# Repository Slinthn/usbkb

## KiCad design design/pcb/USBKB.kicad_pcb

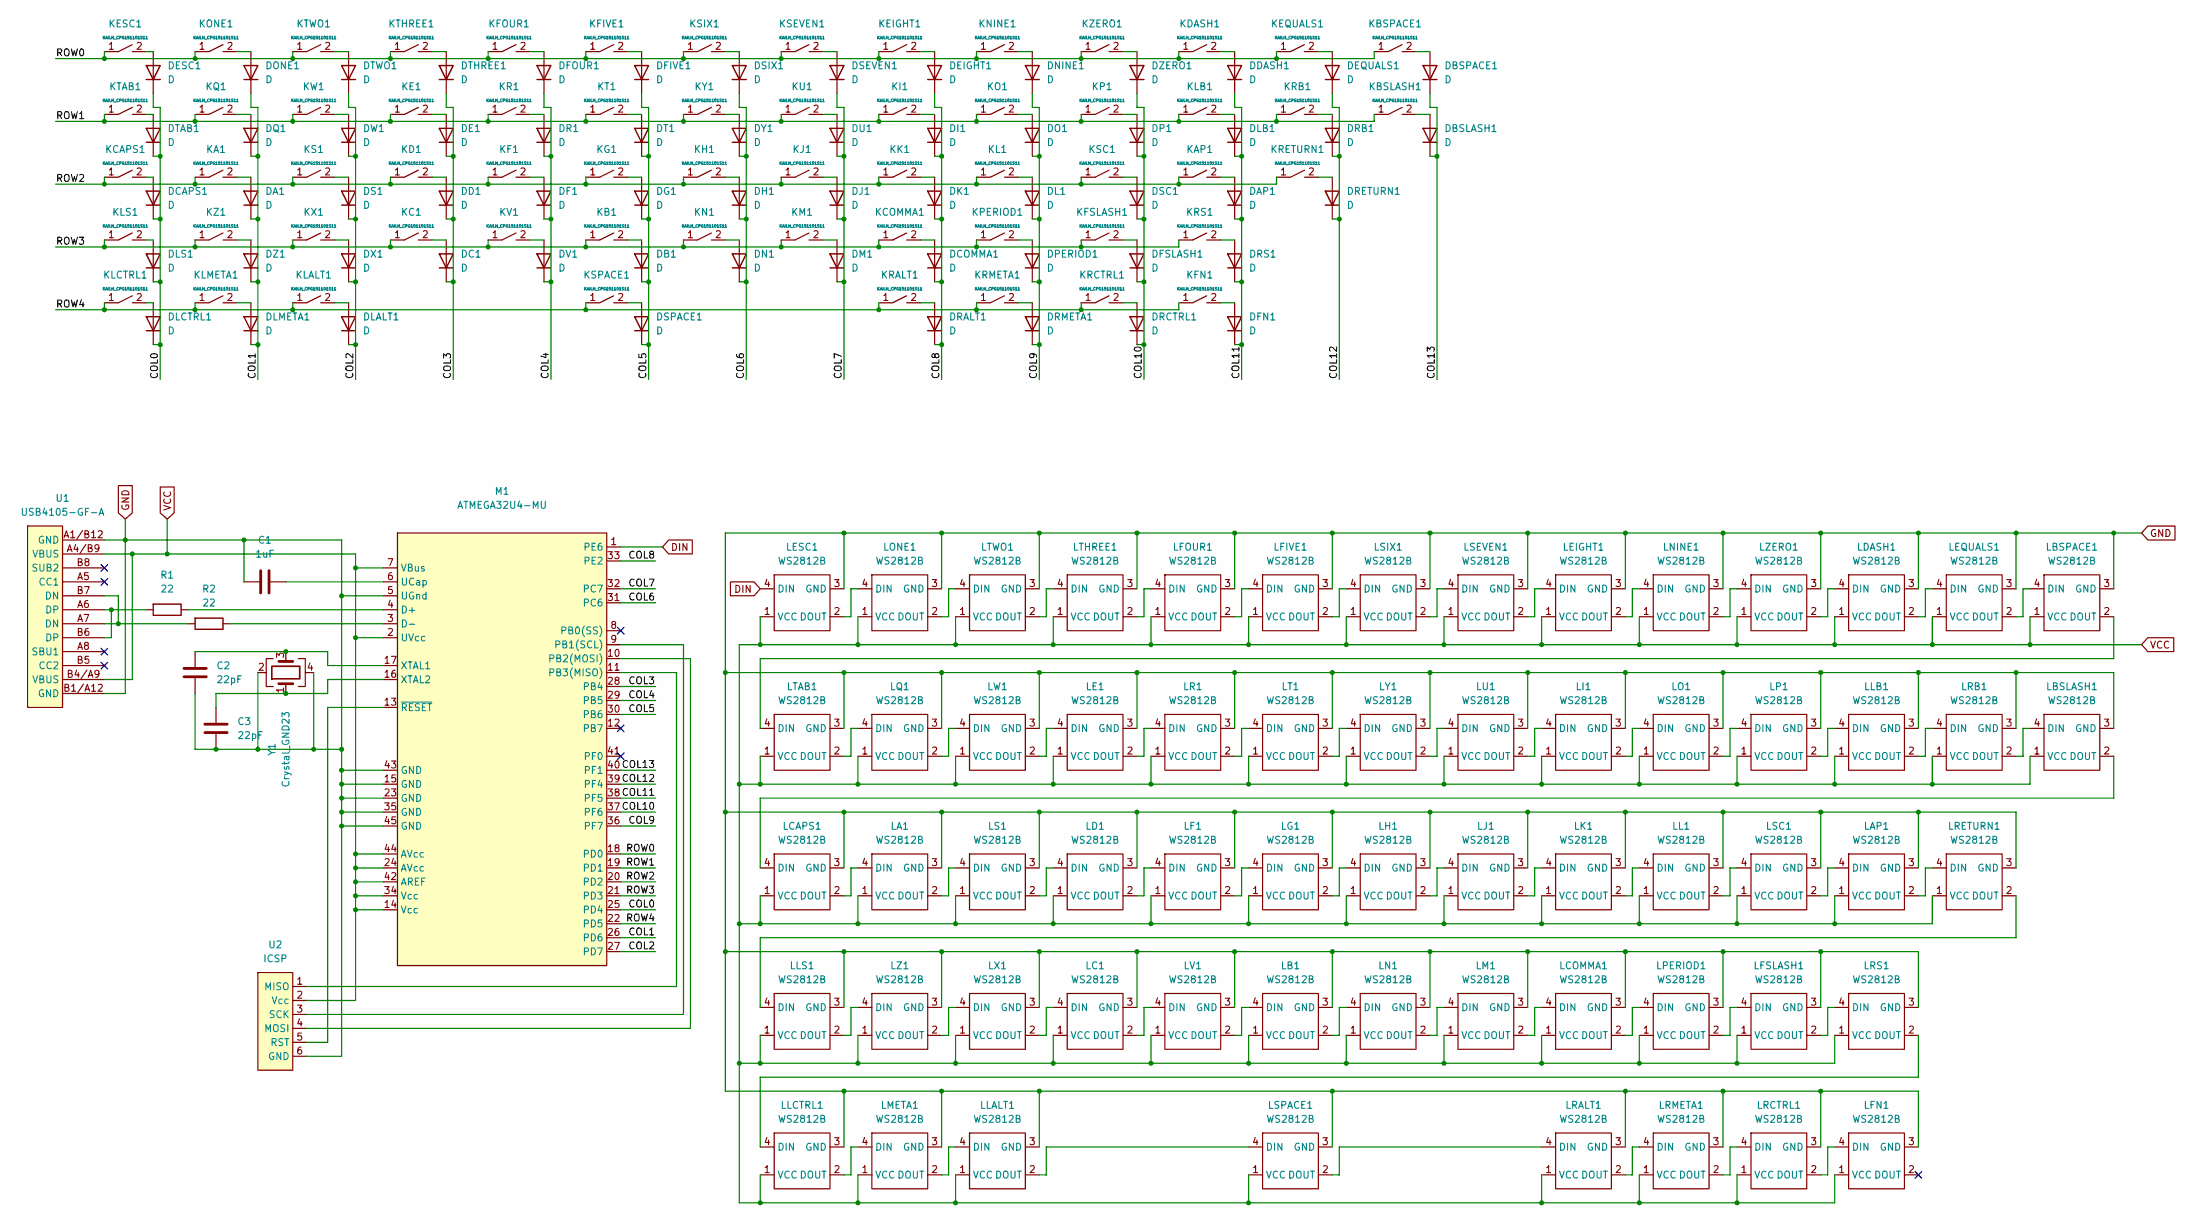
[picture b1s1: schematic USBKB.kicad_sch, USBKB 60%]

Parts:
C1: 1uF; 0805
C2, C3: 22pF; 0805
DA1: D; 1N4148WX
DAP1: D; 1N4148WX
DB1: D; 1N4148WX
DBSLASH1: D; 1N4148WX
DBSPACE1: D; 1N4148WX
DC1: D; 1N4148WX
DCAPS1: D; 1N4148WX
DCOMMA1: D; 1N4148WX
DD1: D; 1N4148WX
DDASH1: D; 1N4148WX
DE1: D; 1N4148WX
DEIGHT1: D; 1N4148WX
DEQUALS1: D; 1N4148WX
DESC1: D; 1N4148WX
DF1: D; 1N4148WX
DFIVE1: D; 1N4148WX
DFN1: D; 1N4148WX
DFOUR1: D; 1N4148WX
DFSLASH1: D; 1N4148WX
DG1: D; 1N4148WX
DH1: D; 1N4148WX
DI1: D; 1N4148WX
DJ1: D; 1N4148WX
DK1: D; 1N4148WX
DL1: D; 1N4148WX
DLALT1: D; 1N4148WX
DLB1: D; 1N4148WX
DLCTRL1: D; 1N4148WX
DLMETA1: D; 1N4148WX
DLS1: D; 1N4148WX
DM1: D; 1N4148WX
DN1: D; 1N4148WX
DNINE1: D; 1N4148WX
DO1: D; 1N4148WX
DONE1: D; 1N4148WX
DP1: D; 1N4148WX
DPERIOD1: D; 1N4148WX
DQ1: D; 1N4148WX
DR1: D; 1N4148WX
DRALT1: D; 1N4148WX
DRB1: D; 1N4148WX
DRCTRL1: D; 1N4148WX
DRETURN1: D; 1N4148WX
DRMETA1: D; 1N4148WX
DRS1: D; 1N4148WX
DS1: D; 1N4148WX
DSC1: D; 1N4148WX
DSEVEN1: D; 1N4148WX
DSIX1: D; 1N4148WX
DSPACE1: D; 1N4148WX
DT1: D; 1N4148WX
DTAB1: D; 1N4148WX
DTHREE1: D; 1N4148WX
DTWO1: D; 1N4148WX
DU1: D; 1N4148WX
DV1: D; 1N4148WX
DW1: D; 1N4148WX
DX1: D; 1N4148WX
DY1: D; 1N4148WX
DZ1: D; 1N4148WX
DZERO1: D; 1N4148WX
KA1: KAILH_CPG151101S11; KAILH-CPG151101S11-1U
KAP1: KAILH_CPG151101S11; KAILH-CPG151101S11-1U
KB1: KAILH_CPG151101S11; KAILH-CPG151101S11-1U
KBSLASH1: KAILH_CPG151101S11; KAILH-CPG151101S11-1.5U
KBSPACE1: KAILH_CPG151101S11; KAILH-CPG151101S11-2U
KC1: KAILH_CPG151101S11; KAILH-CPG151101S11-1U
KCAPS1: KAILH_CPG151101S11; KAILH-CPG151101S11-1.75U
KCOMMA1: KAILH_CPG151101S11; KAILH-CPG151101S11-1U
KD1: KAILH_CPG151101S11; KAILH-CPG151101S11-1U
KDASH1: KAILH_CPG151101S11; KAILH-CPG151101S11-1U
KE1: KAILH_CPG151101S11; KAILH-CPG151101S11-1U
KEIGHT1: KAILH_CPG151101S11; KAILH-CPG151101S11-1U
KEQUALS1: KAILH_CPG151101S11; KAILH-CPG151101S11-1U
KESC1: KAILH_CPG151101S11; KAILH-CPG151101S11-1U
KF1: KAILH_CPG151101S11; KAILH-CPG151101S11-1U
KFIVE1: KAILH_CPG151101S11; KAILH-CPG151101S11-1U
KFN1: KAILH_CPG151101S11; KAILH-CPG151101S11-1.25U
KFOUR1: KAILH_CPG151101S11; KAILH-CPG151101S11-1U
KFSLASH1: KAILH_CPG151101S11; KAILH-CPG151101S11-1U
KG1: KAILH_CPG151101S11; KAILH-CPG151101S11-1U
KH1: KAILH_CPG151101S11; KAILH-CPG151101S11-1U
KI1: KAILH_CPG151101S11; KAILH-CPG151101S11-1U
KJ1: KAILH_CPG151101S11; KAILH-CPG151101S11-1U
KK1: KAILH_CPG151101S11; KAILH-CPG151101S11-1U
KL1: KAILH_CPG151101S11; KAILH-CPG151101S11-1U
KLALT1: KAILH_CPG151101S11; KAILH-CPG151101S11-1.25U
KLB1: KAILH_CPG151101S11; KAILH-CPG151101S11-1U
KLCTRL1: KAILH_CPG151101S11; KAILH-CPG151101S11-1.25U
KLMETA1: KAILH_CPG151101S11; KAILH-CPG151101S11-1.25U
KLS1: KAILH_CPG151101S11; KAILH-CPG151101S11-2.25U
KM1: KAILH_CPG151101S11; KAILH-CPG151101S11-1U
KN1: KAILH_CPG151101S11; KAILH-CPG151101S11-1U
KNINE1: KAILH_CPG151101S11; KAILH-CPG151101S11-1U
KO1: KAILH_CPG151101S11; KAILH-CPG151101S11-1U
KONE1: KAILH_CPG151101S11; KAILH-CPG151101S11-1U
KP1: KAILH_CPG151101S11; KAILH-CPG151101S11-1U
KPERIOD1: KAILH_CPG151101S11; KAILH-CPG151101S11-1U
KQ1: KAILH_CPG151101S11; KAILH-CPG151101S11-1U
KR1: KAILH_CPG151101S11; KAILH-CPG151101S11-1U
KRALT1: KAILH_CPG151101S11; KAILH-CPG151101S11-1.25U
KRB1: KAILH_CPG151101S11; KAILH-CPG151101S11-1U
KRCTRL1: KAILH_CPG151101S11; KAILH-CPG151101S11-1.25U
KRETURN1: KAILH_CPG151101S11; KAILH-CPG151101S11-2.25U
KRMETA1: KAILH_CPG151101S11; KAILH-CPG151101S11-1.25U
KRS1: KAILH_CPG151101S11; KAILH-CPG151101S11-2.75U
KS1: KAILH_CPG151101S11; KAILH-CPG151101S11-1U
KSC1: KAILH_CPG151101S11; KAILH-CPG151101S11-1U
KSEVEN1: KAILH_CPG151101S11; KAILH-CPG151101S11-1U
KSIX1: KAILH_CPG151101S11; KAILH-CPG151101S11-1U
KSPACE1: KAILH_CPG151101S11; KAILH-CPG151101S11-6.25U
KT1: KAILH_CPG151101S11; KAILH-CPG151101S11-1U
KTAB1: KAILH_CPG151101S11; KAILH-CPG151101S11-1.5U
KTHREE1: KAILH_CPG151101S11; KAILH-CPG151101S11-1U
KTWO1: KAILH_CPG151101S11; KAILH-CPG151101S11-1U
KU1: KAILH_CPG151101S11; KAILH-CPG151101S11-1U
KV1: KAILH_CPG151101S11; KAILH-CPG151101S11-1U
KW1: KAILH_CPG151101S11; KAILH-CPG151101S11-1U
KX1: KAILH_CPG151101S11; KAILH-CPG151101S11-1U
KY1: KAILH_CPG151101S11; KAILH-CPG151101S11-1U
KZ1: KAILH_CPG151101S11; KAILH-CPG151101S11-1U
KZERO1: KAILH_CPG151101S11; KAILH-CPG151101S11-1U
LA1: WS2812B; SK6812MINI-E
LAP1: WS2812B; SK6812MINI-E
LB1: WS2812B; SK6812MINI-E
LBSLASH1: WS2812B; SK6812MINI-E
LBSPACE1: WS2812B; SK6812MINI-E
LC1: WS2812B; SK6812MINI-E
LCAPS1: WS2812B; SK6812MINI-E
LCOMMA1: WS2812B; SK6812MINI-E
LD1: WS2812B; SK6812MINI-E
LDASH1: WS2812B; SK6812MINI-E
LE1: WS2812B; SK6812MINI-E
LEIGHT1: WS2812B; SK6812MINI-E
LEQUALS1: WS2812B; SK6812MINI-E
LESC1: WS2812B; SK6812MINI-E
LF1: WS2812B; SK6812MINI-E
LFIVE1: WS2812B; SK6812MINI-E
LFN1: WS2812B; SK6812MINI-E
LFOUR1: WS2812B; SK6812MINI-E
LFSLASH1: WS2812B; SK6812MINI-E
LG1: WS2812B; SK6812MINI-E
LH1: WS2812B; SK6812MINI-E
LI1: WS2812B; SK6812MINI-E
LJ1: WS2812B; SK6812MINI-E
LK1: WS2812B; SK6812MINI-E
LL1: WS2812B; SK6812MINI-E
LLALT1: WS2812B; SK6812MINI-E
LLB1: WS2812B; SK6812MINI-E
LLCTRL1: WS2812B; SK6812MINI-E
LLS1: WS2812B; SK6812MINI-E
LM1: WS2812B; SK6812MINI-E
LMETA1: WS2812B; SK6812MINI-E
LN1: WS2812B; SK6812MINI-E
LNINE1: WS2812B; SK6812MINI-E
LO1: WS2812B; SK6812MINI-E
LONE1: WS2812B; SK6812MINI-E
LP1: WS2812B; SK6812MINI-E
LPERIOD1: WS2812B; SK6812MINI-E
LQ1: WS2812B; SK6812MINI-E
LR1: WS2812B; SK6812MINI-E
LRALT1: WS2812B; SK6812MINI-E
LRB1: WS2812B; SK6812MINI-E
LRCTRL1: WS2812B; SK6812MINI-E
LRETURN1: WS2812B; SK6812MINI-E
LRMETA1: WS2812B; SK6812MINI-E
LRS1: WS2812B; SK6812MINI-E
LS1: WS2812B; SK6812MINI-E
LSC1: WS2812B; SK6812MINI-E
LSEVEN1: WS2812B; SK6812MINI-E
LSIX1: WS2812B; SK6812MINI-E
LSPACE1: WS2812B; SK6812MINI-E
LT1: WS2812B; SK6812MINI-E
LTAB1: WS2812B; SK6812MINI-E
LTHREE1: WS2812B; SK6812MINI-E
LTWO1: WS2812B; SK6812MINI-E
LU1: WS2812B; SK6812MINI-E
LV1: WS2812B; SK6812MINI-E
LW1: WS2812B; SK6812MINI-E
LX1: WS2812B; SK6812MINI-E
LY1: WS2812B; SK6812MINI-E
LZ1: WS2812B; SK6812MINI-E
LZERO1: WS2812B; SK6812MINI-E
M1: ATMEGA32U4-MU
R1, R2: 22; 0805
U1: USB4105-GF-A
U2: ICSP
Y1: Crystal_GND23; ABM8G

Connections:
/COL0: DCAPS1.1 (K), DESC1.1 (K), DLCTRL1.1 (K), DLS1.1 (K), DTAB1.1 (K), M1.25 (PD4)
/COL1: DA1.1 (K), DLMETA1.1 (K), DONE1.1 (K), DQ1.1 (K), DZ1.1 (K), M1.26 (PD6)
/COL2: DLALT1.1 (K), DS1.1 (K), DTWO1.1 (K), DW1.1 (K), DX1.1 (K), M1.27 (PD7)
/COL3: DC1.1 (K), DD1.1 (K), DE1.1 (K), DTHREE1.1 (K), M1.28 (PB4)
/COL4: DF1.1 (K), DFOUR1.1 (K), DR1.1 (K), DV1.1 (K), M1.29 (PB5)
/COL5: DB1.1 (K), DFIVE1.1 (K), DG1.1 (K), DSPACE1.1 (K), DT1.1 (K), M1.30 (PB6)
/COL6: DH1.1 (K), DN1.1 (K), DSIX1.1 (K), DY1.1 (K), M1.31 (PC6)
/COL7: DJ1.1 (K), DM1.1 (K), DSEVEN1.1 (K), DU1.1 (K), M1.32 (PC7)
/COL8: DCOMMA1.1 (K), DEIGHT1.1 (K), DI1.1 (K), DK1.1 (K), DRALT1.1 (K), M1.33 (PE2)
/COL9: DL1.1 (K), DNINE1.1 (K), DO1.1 (K), DPERIOD1.1 (K), DRMETA1.1 (K), M1.36 (PF7)
/COL10: DFSLASH1.1 (K), DP1.1 (K), DRCTRL1.1 (K), DSC1.1 (K), DZERO1.1 (K), M1.37 (PF6)
/COL11: DAP1.1 (K), DDASH1.1 (K), DFN1.1 (K), DLB1.1 (K), DRS1.1 (K), M1.38 (PF5)
/COL12: DEQUALS1.1 (K), DRB1.1 (K), DRETURN1.1 (K), M1.39 (PF4)
/COL13: DBSLASH1.1 (K), DBSPACE1.1 (K), M1.40 (PF1)
/ROW0: KBSPACE1.1, KDASH1.1, KEIGHT1.1, KEQUALS1.1, KESC1.1, KFIVE1.1, KFOUR1.1, KNINE1.1, KONE1.1, KSEVEN1.1, KSIX1.1, KTHREE1.1, KTWO1.1, KZERO1.1, M1.18 (PD0)
/ROW1: KBSLASH1.1, KE1.1, KI1.1, KLB1.1, KO1.1, KP1.1, KQ1.1, KR1.1, KRB1.1, KT1.1, KTAB1.1, KU1.1, KW1.1, KY1.1, M1.19 (PD1)
/ROW2: KA1.1, KAP1.1, KCAPS1.1, KD1.1, KF1.1, KG1.1, KH1.1, KJ1.1, KK1.1, KL1.1, KRETURN1.1, KS1.1, KSC1.1, M1.20 (PD2)
/ROW3: KB1.1, KC1.1, KCOMMA1.1, KFSLASH1.1, KLS1.1, KM1.1, KN1.1, KPERIOD1.1, KRS1.1, KV1.1, KX1.1, KZ1.1, M1.21 (PD3)
/ROW4: KFN1.1, KLALT1.1, KLCTRL1.1, KLMETA1.1, KRALT1.1, KRCTRL1.1, KRMETA1.1, KSPACE1.1, M1.22 (PD5)
DIN: LESC1.4 (DIN), M1.1 (PE6)
GND: C1.1, C2.1, C3.2, LA1.3 (GND), LAP1.3 (GND), LB1.3 (GND), LBSLASH1.3 (GND), LBSPACE1.3 (GND), LC1.3 (GND), LCAPS1.3 (GND), LCOMMA1.3 (GND), LD1.3 (GND), LDASH1.3 (GND), LE1.3 (GND), LEIGHT1.3 (GND), LEQUALS1.3 (GND), LESC1.3 (GND), LF1.3 (GND), LFIVE1.3 (GND), LFN1.3 (GND), LFOUR1.3 (GND), LFSLASH1.3 (GND), LG1.3 (GND), LH1.3 (GND), LI1.3 (GND), LJ1.3 (GND), LK1.3 (GND), LL1.3 (GND), LLALT1.3 (GND), LLB1.3 (GND), LLCTRL1.3 (GND), LLS1.3 (GND), LM1.3 (GND), LMETA1.3 (GND), LN1.3 (GND), LNINE1.3 (GND), LO1.3 (GND), LONE1.3 (GND), LP1.3 (GND), LPERIOD1.3 (GND), LQ1.3 (GND), LR1.3 (GND), LRALT1.3 (GND), LRB1.3 (GND), LRCTRL1.3 (GND), LRETURN1.3 (GND), LRMETA1.3 (GND), LRS1.3 (GND), LS1.3 (GND), LSC1.3 (GND), LSEVEN1.3 (GND), LSIX1.3 (GND), LSPACE1.3 (GND), LT1.3 (GND), LTAB1.3 (GND), LTHREE1.3 (GND), LTWO1.3 (GND), LU1.3 (GND), LV1.3 (GND), LW1.3 (GND), LX1.3 (GND), LY1.3 (GND), LZ1.3 (GND), LZERO1.3 (GND), M1.5 (UGnd), M1.15 (GND), M1.23 (GND), M1.35 (GND), M1.43 (GND), M1.45 (GND), U1.A1/B12 (GND), U1.B1/A12 (GND), U2.6 (GND), Y1.2, Y1.4
unnamed: C1.2, M1.6 (UCap)
unnamed: C2.2, M1.17 (XTAL1), Y1.3
unnamed: C3.1, M1.16 (XTAL2), Y1.1
unnamed: DA1.2 (A), KA1.2
unnamed: DAP1.2 (A), KAP1.2
unnamed: DB1.2 (A), KB1.2
unnamed: DBSLASH1.2 (A), KBSLASH1.2
unnamed: DBSPACE1.2 (A), KBSPACE1.2
unnamed: DC1.2 (A), KC1.2
unnamed: DCAPS1.2 (A), KCAPS1.2
unnamed: DCOMMA1.2 (A), KCOMMA1.2
unnamed: DD1.2 (A), KD1.2
unnamed: DDASH1.2 (A), KDASH1.2
unnamed: DE1.2 (A), KE1.2
unnamed: DEIGHT1.2 (A), KEIGHT1.2
unnamed: DEQUALS1.2 (A), KEQUALS1.2
unnamed: DESC1.2 (A), KESC1.2
unnamed: DF1.2 (A), KF1.2
unnamed: DFIVE1.2 (A), KFIVE1.2
unnamed: DFN1.2 (A), KFN1.2
unnamed: DFOUR1.2 (A), KFOUR1.2
unnamed: DFSLASH1.2 (A), KFSLASH1.2
unnamed: DG1.2 (A), KG1.2
unnamed: DH1.2 (A), KH1.2
unnamed: DI1.2 (A), KI1.2
unnamed: DJ1.2 (A), KJ1.2
unnamed: DK1.2 (A), KK1.2
unnamed: DL1.2 (A), KL1.2
unnamed: DLALT1.2 (A), KLALT1.2
unnamed: DLB1.2 (A), KLB1.2
unnamed: DLCTRL1.2 (A), KLCTRL1.2
unnamed: DLMETA1.2 (A), KLMETA1.2
unnamed: DLS1.2 (A), KLS1.2
unnamed: DM1.2 (A), KM1.2
unnamed: DN1.2 (A), KN1.2
unnamed: DNINE1.2 (A), KNINE1.2
unnamed: DO1.2 (A), KO1.2
unnamed: DONE1.2 (A), KONE1.2
unnamed: DP1.2 (A), KP1.2
unnamed: DPERIOD1.2 (A), KPERIOD1.2
unnamed: DQ1.2 (A), KQ1.2
unnamed: DR1.2 (A), KR1.2
unnamed: DRALT1.2 (A), KRALT1.2
unnamed: DRB1.2 (A), KRB1.2
unnamed: DRCTRL1.2 (A), KRCTRL1.2
unnamed: DRETURN1.2 (A), KRETURN1.2
unnamed: DRMETA1.2 (A), KRMETA1.2
unnamed: DRS1.2 (A), KRS1.2
unnamed: DS1.2 (A), KS1.2
unnamed: DSC1.2 (A), KSC1.2
unnamed: DSEVEN1.2 (A), KSEVEN1.2
unnamed: DSIX1.2 (A), KSIX1.2
unnamed: DSPACE1.2 (A), KSPACE1.2
unnamed: DT1.2 (A), KT1.2
unnamed: DTAB1.2 (A), KTAB1.2
unnamed: DTHREE1.2 (A), KTHREE1.2
unnamed: DTWO1.2 (A), KTWO1.2
unnamed: DU1.2 (A), KU1.2
unnamed: DV1.2 (A), KV1.2
unnamed: DW1.2 (A), KW1.2
unnamed: DX1.2 (A), KX1.2
unnamed: DY1.2 (A), KY1.2
unnamed: DZ1.2 (A), KZ1.2
unnamed: DZERO1.2 (A), KZERO1.2
unnamed: LA1.2 (DOUT), LS1.4 (DIN)
unnamed: LA1.4 (DIN), LCAPS1.2 (DOUT)
unnamed: LAP1.2 (DOUT), LRETURN1.4 (DIN)
unnamed: LAP1.4 (DIN), LSC1.2 (DOUT)
unnamed: LB1.2 (DOUT), LN1.4 (DIN)
unnamed: LB1.4 (DIN), LV1.2 (DOUT)
unnamed: LBSLASH1.2 (DOUT), LCAPS1.4 (DIN)
unnamed: LBSLASH1.4 (DIN), LRB1.2 (DOUT)
unnamed: LBSPACE1.2 (DOUT), LTAB1.4 (DIN)
unnamed: LBSPACE1.4 (DIN), LEQUALS1.2 (DOUT)
unnamed: LC1.2 (DOUT), LV1.4 (DIN)
unnamed: LC1.4 (DIN), LX1.2 (DOUT)
unnamed: LCOMMA1.2 (DOUT), LPERIOD1.4 (DIN)
unnamed: LCOMMA1.4 (DIN), LM1.2 (DOUT)
unnamed: LD1.2 (DOUT), LF1.4 (DIN)
unnamed: LD1.4 (DIN), LS1.2 (DOUT)
unnamed: LDASH1.2 (DOUT), LEQUALS1.4 (DIN)
unnamed: LDASH1.4 (DIN), LZERO1.2 (DOUT)
unnamed: LE1.2 (DOUT), LR1.4 (DIN)
unnamed: LE1.4 (DIN), LW1.2 (DOUT)
unnamed: LEIGHT1.2 (DOUT), LNINE1.4 (DIN)
unnamed: LEIGHT1.4 (DIN), LSEVEN1.2 (DOUT)
unnamed: LESC1.2 (DOUT), LONE1.4 (DIN)
unnamed: LF1.2 (DOUT), LG1.4 (DIN)
unnamed: LFIVE1.2 (DOUT), LSIX1.4 (DIN)
unnamed: LFIVE1.4 (DIN), LFOUR1.2 (DOUT)
unnamed: LFN1.4 (DIN), LRCTRL1.2 (DOUT)
unnamed: LFOUR1.4 (DIN), LTHREE1.2 (DOUT)
unnamed: LFSLASH1.2 (DOUT), LRS1.4 (DIN)
unnamed: LFSLASH1.4 (DIN), LPERIOD1.2 (DOUT)
unnamed: LG1.2 (DOUT), LH1.4 (DIN)
unnamed: LH1.2 (DOUT), LJ1.4 (DIN)
unnamed: LI1.2 (DOUT), LO1.4 (DIN)
unnamed: LI1.4 (DIN), LU1.2 (DOUT)
unnamed: LJ1.2 (DOUT), LK1.4 (DIN)
unnamed: LK1.2 (DOUT), LL1.4 (DIN)
unnamed: LL1.2 (DOUT), LSC1.4 (DIN)
unnamed: LLALT1.2 (DOUT), LSPACE1.4 (DIN)
unnamed: LLALT1.4 (DIN), LMETA1.2 (DOUT)
unnamed: LLB1.2 (DOUT), LRB1.4 (DIN)
unnamed: LLB1.4 (DIN), LP1.2 (DOUT)
unnamed: LLCTRL1.2 (DOUT), LMETA1.4 (DIN)
unnamed: LLCTRL1.4 (DIN), LRS1.2 (DOUT)
unnamed: LLS1.2 (DOUT), LZ1.4 (DIN)
unnamed: LLS1.4 (DIN), LRETURN1.2 (DOUT)
unnamed: LM1.4 (DIN), LN1.2 (DOUT)
unnamed: LNINE1.2 (DOUT), LZERO1.4 (DIN)
unnamed: LO1.2 (DOUT), LP1.4 (DIN)
unnamed: LONE1.2 (DOUT), LTWO1.4 (DIN)
unnamed: LQ1.2 (DOUT), LW1.4 (DIN)
unnamed: LQ1.4 (DIN), LTAB1.2 (DOUT)
unnamed: LR1.2 (DOUT), LT1.4 (DIN)
unnamed: LRALT1.2 (DOUT), LRMETA1.4 (DIN)
unnamed: LRALT1.4 (DIN), LSPACE1.2 (DOUT)
unnamed: LRCTRL1.4 (DIN), LRMETA1.2 (DOUT)
unnamed: LSEVEN1.4 (DIN), LSIX1.2 (DOUT)
unnamed: LT1.2 (DOUT), LY1.4 (DIN)
unnamed: LTHREE1.4 (DIN), LTWO1.2 (DOUT)
unnamed: LU1.4 (DIN), LY1.2 (DOUT)
unnamed: LX1.4 (DIN), LZ1.2 (DOUT)
unnamed: M1.3 (D-), R2.1
unnamed: M1.4 (D+), R1.1
unnamed: M1.9 (PB1(SCL)), U2.3 (SCK)
unnamed: M1.10 (PB2(MOSI)), U2.4 (MOSI)
unnamed: M1.11 (PB3(MISO)), U2.1 (MISO)
unnamed: M1.13 (~RESET), U2.5 (RST)
unnamed: R1.2, U1.A6 (DP), U1.B6 (DP)
unnamed: R2.2, U1.A7 (DN), U1.B7 (DN)
VCC: LA1.1 (VCC), LAP1.1 (VCC), LB1.1 (VCC), LBSLASH1.1 (VCC), LBSPACE1.1 (VCC), LC1.1 (VCC), LCAPS1.1 (VCC), LCOMMA1.1 (VCC), LD1.1 (VCC), LDASH1.1 (VCC), LE1.1 (VCC), LEIGHT1.1 (VCC), LEQUALS1.1 (VCC), LESC1.1 (VCC), LF1.1 (VCC), LFIVE1.1 (VCC), LFN1.1 (VCC), LFOUR1.1 (VCC), LFSLASH1.1 (VCC), LG1.1 (VCC), LH1.1 (VCC), LI1.1 (VCC), LJ1.1 (VCC), LK1.1 (VCC), LL1.1 (VCC), LLALT1.1 (VCC), LLB1.1 (VCC), LLCTRL1.1 (VCC), LLS1.1 (VCC), LM1.1 (VCC), LMETA1.1 (VCC), LN1.1 (VCC), LNINE1.1 (VCC), LO1.1 (VCC), LONE1.1 (VCC), LP1.1 (VCC), LPERIOD1.1 (VCC), LQ1.1 (VCC), LR1.1 (VCC), LRALT1.1 (VCC), LRB1.1 (VCC), LRCTRL1.1 (VCC), LRETURN1.1 (VCC), LRMETA1.1 (VCC), LRS1.1 (VCC), LS1.1 (VCC), LSC1.1 (VCC), LSEVEN1.1 (VCC), LSIX1.1 (VCC), LSPACE1.1 (VCC), LT1.1 (VCC), LTAB1.1 (VCC), LTHREE1.1 (VCC), LTWO1.1 (VCC), LU1.1 (VCC), LV1.1 (VCC), LW1.1 (VCC), LX1.1 (VCC), LY1.1 (VCC), LZ1.1 (VCC), LZERO1.1 (VCC), M1.2 (UVcc), M1.7 (VBus), M1.14 (Vcc), M1.24 (AVcc), M1.34 (Vcc), M1.42 (AREF), M1.44 (AVcc), U1.A4/B9 (VBUS), U1.B4/A9 (VBUS), U2.2 (Vcc)

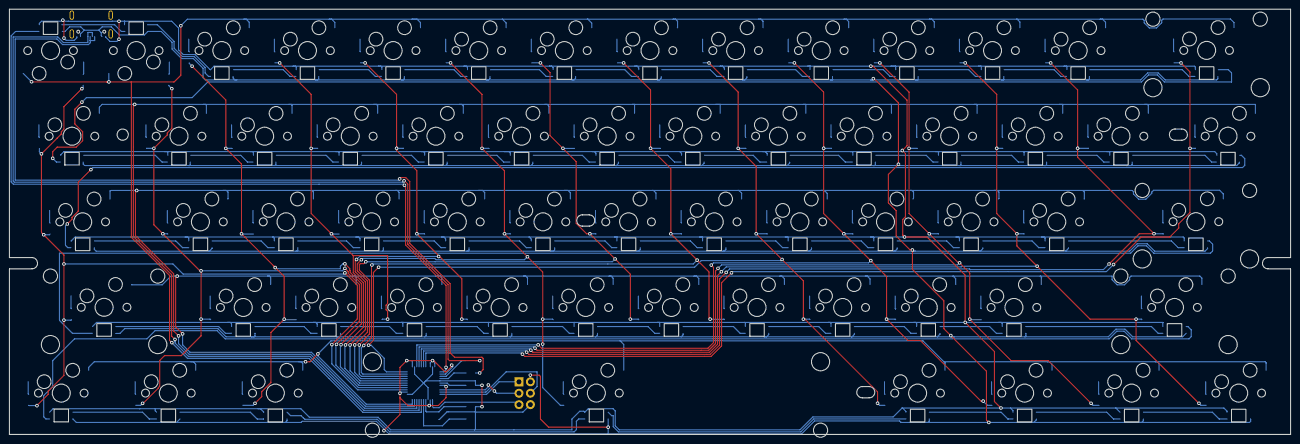
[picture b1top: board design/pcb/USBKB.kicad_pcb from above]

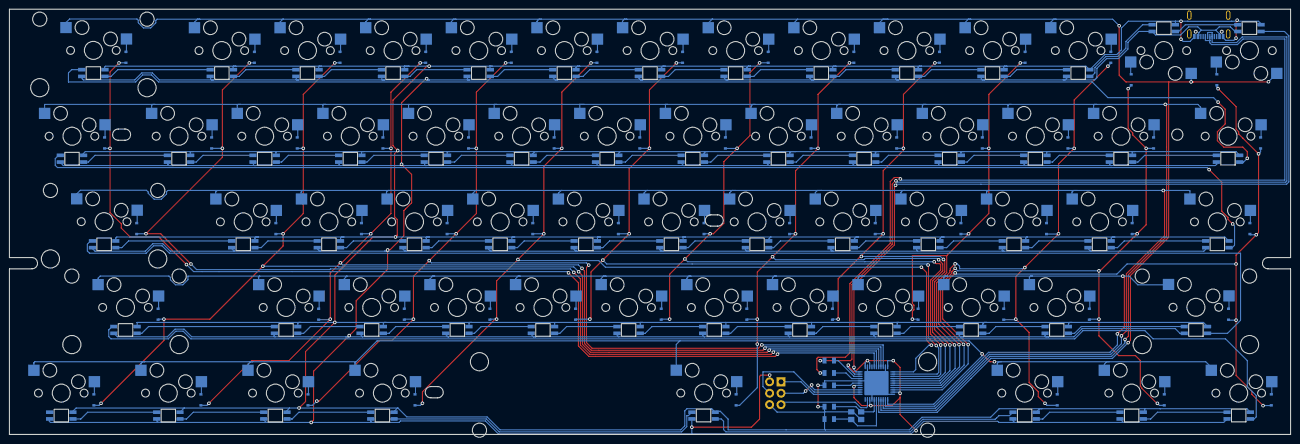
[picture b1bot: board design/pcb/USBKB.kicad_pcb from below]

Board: 2 copper layers, 285.0 x 94.6 mm, 192 parts (130 on the bottom side), 154 nets.

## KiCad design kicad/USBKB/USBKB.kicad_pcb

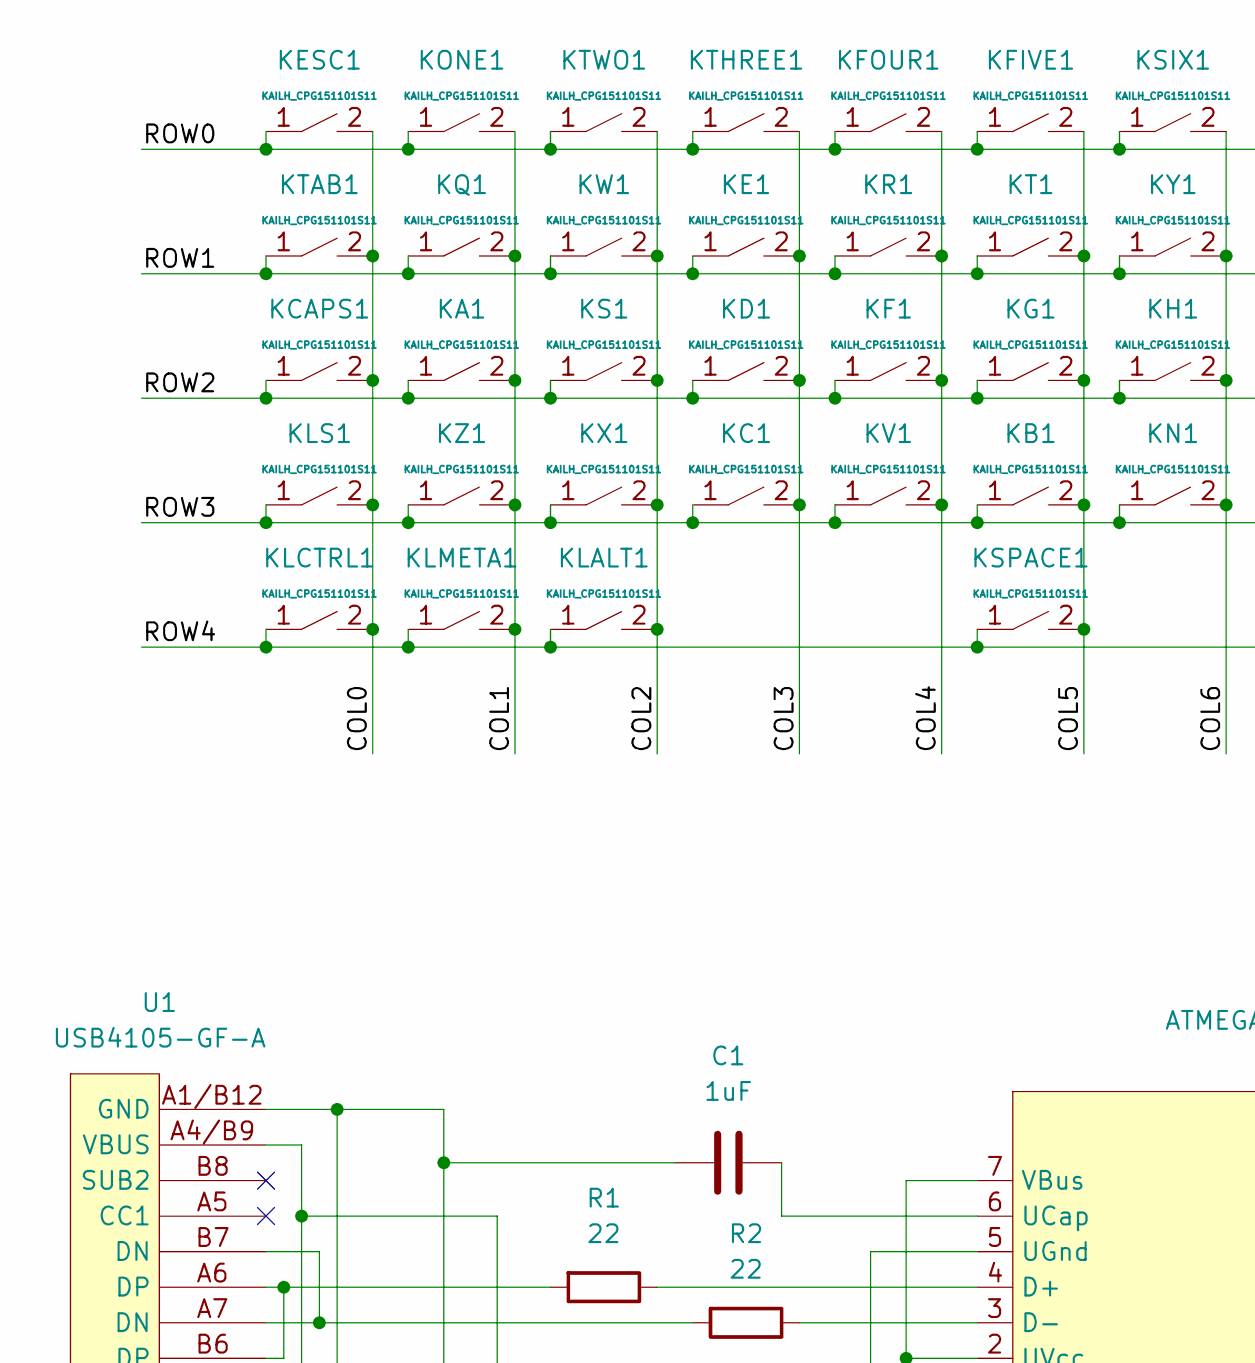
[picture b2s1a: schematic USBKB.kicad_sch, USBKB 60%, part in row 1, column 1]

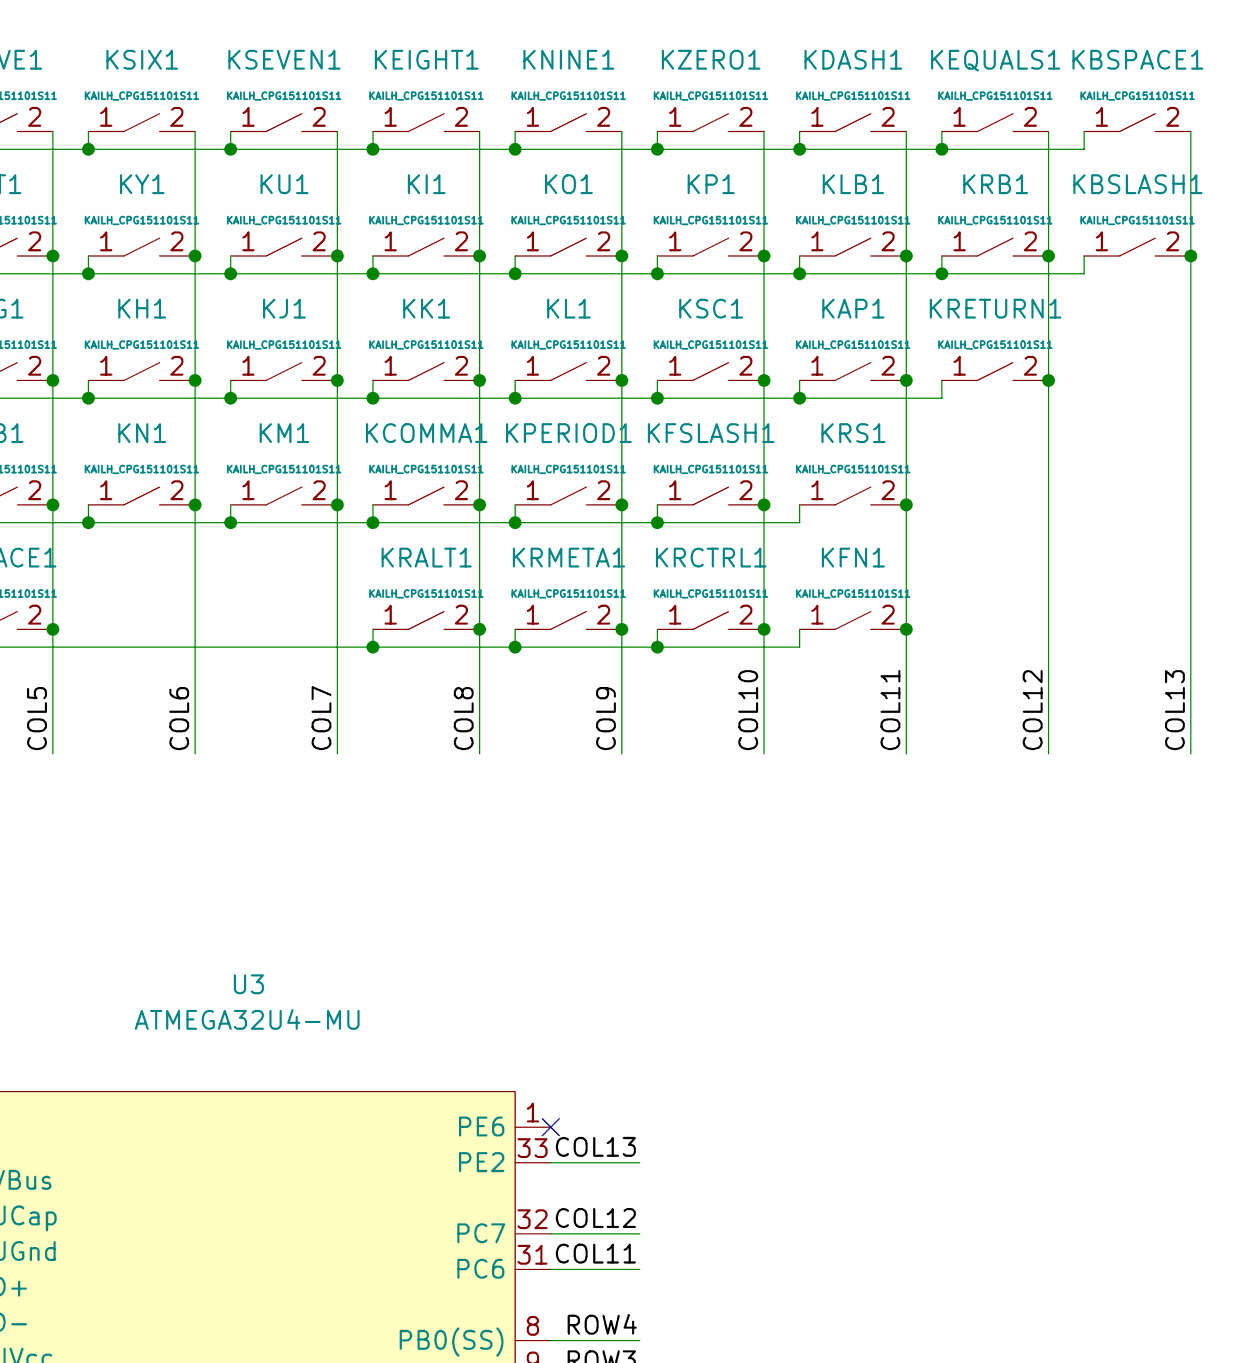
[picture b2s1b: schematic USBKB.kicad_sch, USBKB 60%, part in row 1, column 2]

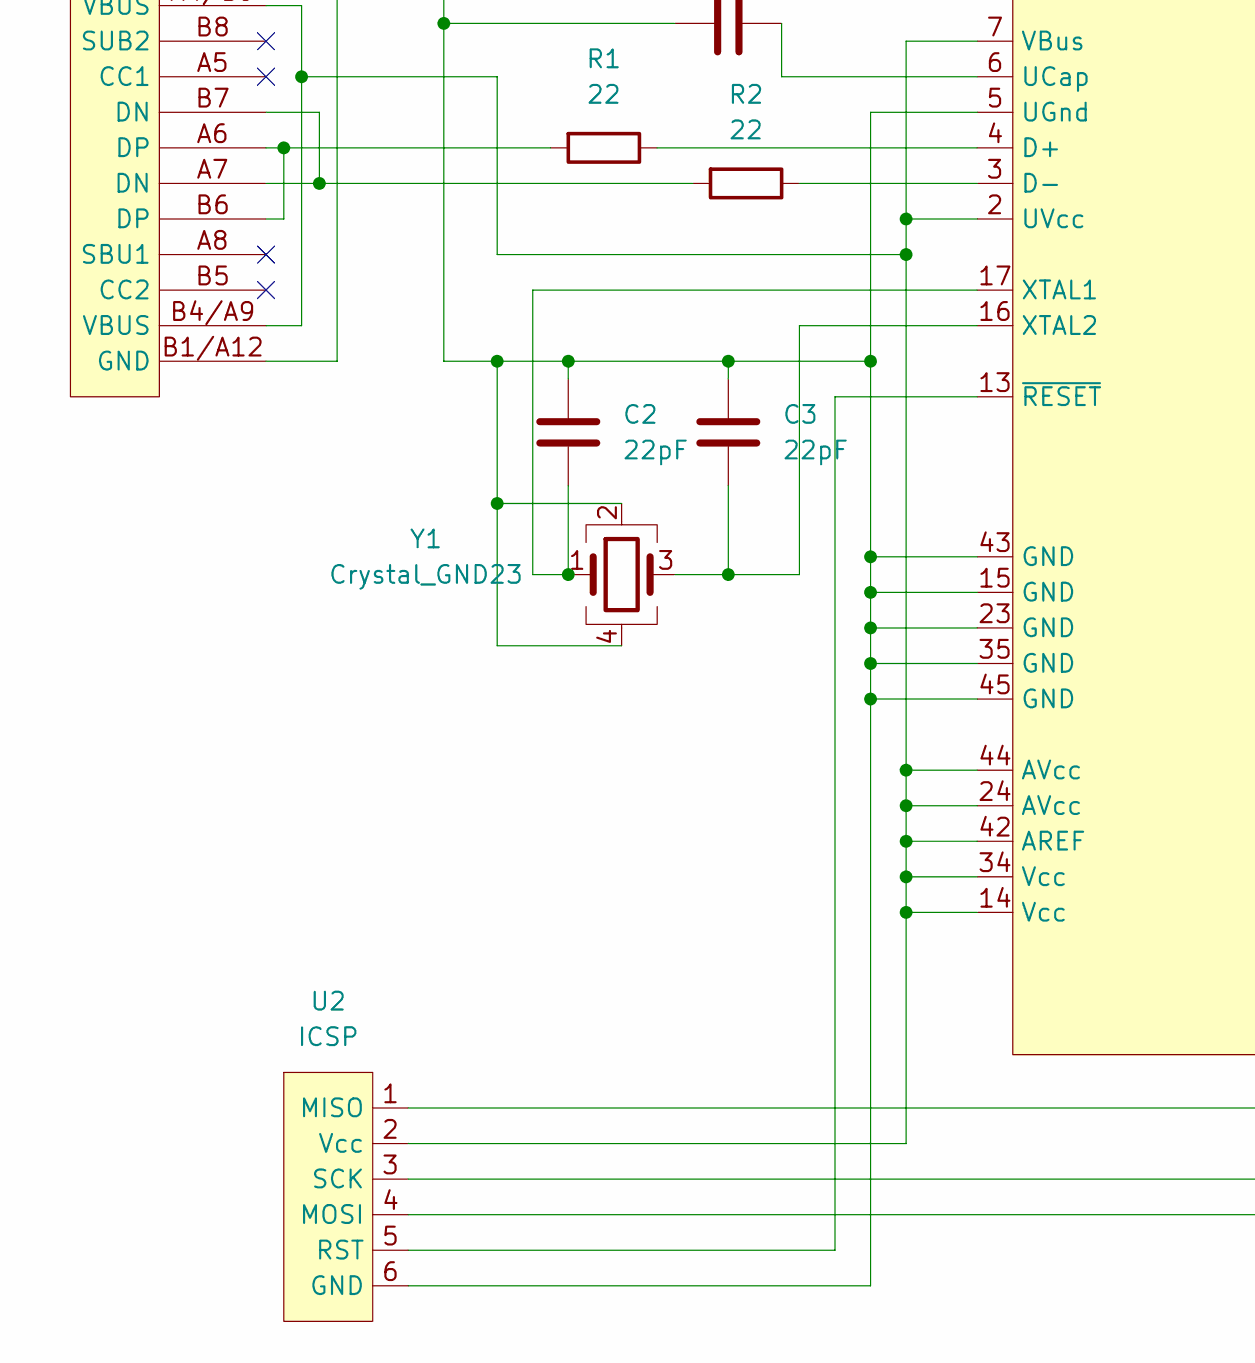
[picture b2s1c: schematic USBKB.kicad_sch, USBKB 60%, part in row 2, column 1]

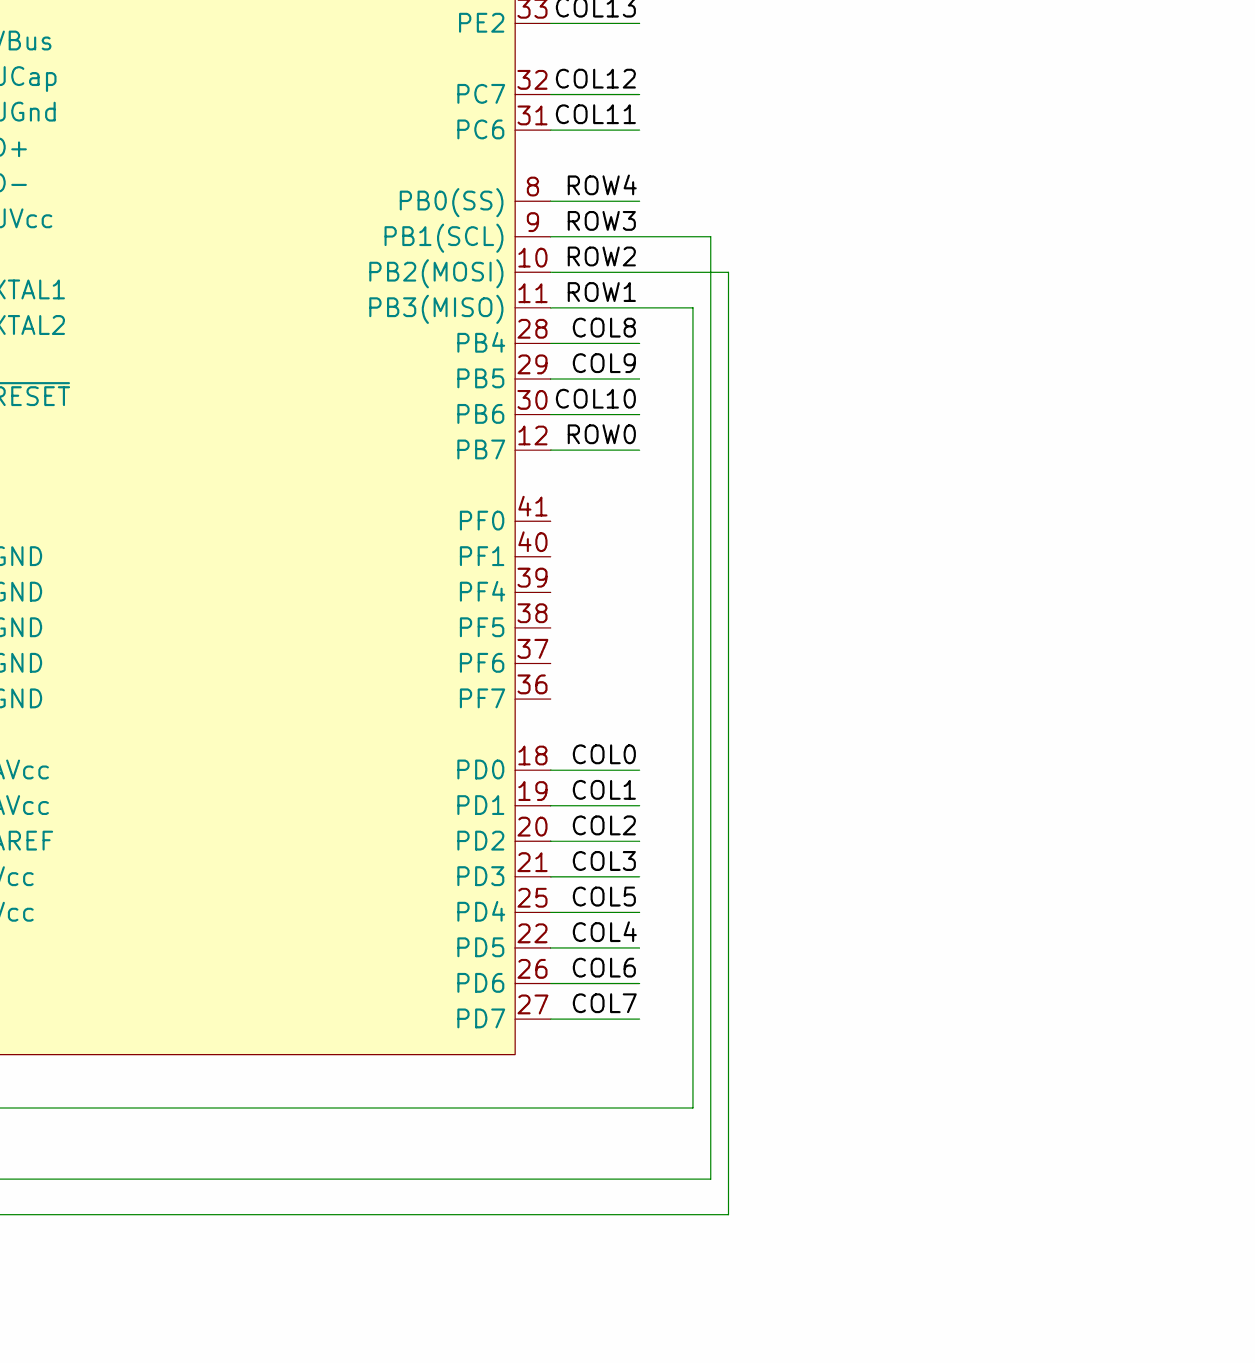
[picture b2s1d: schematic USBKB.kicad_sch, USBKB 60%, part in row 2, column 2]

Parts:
C1: 1uF; 0805
C2, C3: 22pF; 0805
KA1: KAILH_CPG151101S11; KAILH-CPG151101S11-1U
KAP1: KAILH_CPG151101S11; KAILH-CPG151101S11-1U
KB1: KAILH_CPG151101S11; KAILH-CPG151101S11-1U
KBSLASH1: KAILH_CPG151101S11; KAILH-CPG151101S11-1.5U
KBSPACE1: KAILH_CPG151101S11; KAILH-CPG151101S11-2U
KC1: KAILH_CPG151101S11; KAILH-CPG151101S11-1U
KCAPS1: KAILH_CPG151101S11; KAILH-CPG151101S11-1.75U
KCOMMA1: KAILH_CPG151101S11; KAILH-CPG151101S11-1U
KD1: KAILH_CPG151101S11; KAILH-CPG151101S11-1U
KDASH1: KAILH_CPG151101S11; KAILH-CPG151101S11-1U
KE1: KAILH_CPG151101S11; KAILH-CPG151101S11-1U
KEIGHT1: KAILH_CPG151101S11; KAILH-CPG151101S11-1U
KEQUALS1: KAILH_CPG151101S11; KAILH-CPG151101S11-1U
KESC1: KAILH_CPG151101S11; KAILH-CPG151101S11-1U
KF1: KAILH_CPG151101S11; KAILH-CPG151101S11-1U
KFIVE1: KAILH_CPG151101S11; KAILH-CPG151101S11-1U
KFN1: KAILH_CPG151101S11; KAILH-CPG151101S11-1.25U
KFOUR1: KAILH_CPG151101S11; KAILH-CPG151101S11-1U
KFSLASH1: KAILH_CPG151101S11; KAILH-CPG151101S11-1U
KG1: KAILH_CPG151101S11; KAILH-CPG151101S11-1U
KH1: KAILH_CPG151101S11; KAILH-CPG151101S11-1U
KI1: KAILH_CPG151101S11; KAILH-CPG151101S11-1U
KJ1: KAILH_CPG151101S11; KAILH-CPG151101S11-1U
KK1: KAILH_CPG151101S11; KAILH-CPG151101S11-1U
KL1: KAILH_CPG151101S11; KAILH-CPG151101S11-1U
KLALT1: KAILH_CPG151101S11; KAILH-CPG151101S11-1.25U
KLB1: KAILH_CPG151101S11; KAILH-CPG151101S11-1U
KLCTRL1: KAILH_CPG151101S11; KAILH-CPG151101S11-1.25U
KLMETA1: KAILH_CPG151101S11; KAILH-CPG151101S11-1.25U
KLS1: KAILH_CPG151101S11; KAILH-CPG151101S11-2.25U
KM1: KAILH_CPG151101S11; KAILH-CPG151101S11-1U
KN1: KAILH_CPG151101S11; KAILH-CPG151101S11-1U
KNINE1: KAILH_CPG151101S11; KAILH-CPG151101S11-1U
KO1: KAILH_CPG151101S11; KAILH-CPG151101S11-1U
KONE1: KAILH_CPG151101S11; KAILH-CPG151101S11-1U
KP1: KAILH_CPG151101S11; KAILH-CPG151101S11-1U
KPERIOD1: KAILH_CPG151101S11; KAILH-CPG151101S11-1U
KQ1: KAILH_CPG151101S11; KAILH-CPG151101S11-1U
KR1: KAILH_CPG151101S11; KAILH-CPG151101S11-1U
KRALT1: KAILH_CPG151101S11; KAILH-CPG151101S11-1.25U
KRB1: KAILH_CPG151101S11; KAILH-CPG151101S11-1U
KRCTRL1: KAILH_CPG151101S11; KAILH-CPG151101S11-1.25U
KRETURN1: KAILH_CPG151101S11; KAILH-CPG151101S11-2.25U
KRMETA1: KAILH_CPG151101S11; KAILH-CPG151101S11-1.25U
KRS1: KAILH_CPG151101S11; KAILH-CPG151101S11-2.75U
KS1: KAILH_CPG151101S11; KAILH-CPG151101S11-1U
KSC1: KAILH_CPG151101S11; KAILH-CPG151101S11-1U
KSEVEN1: KAILH_CPG151101S11; KAILH-CPG151101S11-1U
KSIX1: KAILH_CPG151101S11; KAILH-CPG151101S11-1U
KSPACE1: KAILH_CPG151101S11; KAILH-CPG151101S11-6.25U
KT1: KAILH_CPG151101S11; KAILH-CPG151101S11-1U
KTAB1: KAILH_CPG151101S11; KAILH-CPG151101S11-1.5U
KTHREE1: KAILH_CPG151101S11; KAILH-CPG151101S11-1U
KTWO1: KAILH_CPG151101S11; KAILH-CPG151101S11-1U
KU1: KAILH_CPG151101S11; KAILH-CPG151101S11-1U
KV1: KAILH_CPG151101S11; KAILH-CPG151101S11-1U
KW1: KAILH_CPG151101S11; KAILH-CPG151101S11-1U
KX1: KAILH_CPG151101S11; KAILH-CPG151101S11-1U
KY1: KAILH_CPG151101S11; KAILH-CPG151101S11-1U
KZ1: KAILH_CPG151101S11; KAILH-CPG151101S11-1U
KZERO1: KAILH_CPG151101S11; KAILH-CPG151101S11-1U
R1, R2: 22; 0805
U1: USB4105-GF-A
U2: ICSP
U3: ATMEGA32U4-MU
Y1: Crystal_GND23; ABM8G

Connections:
/COL0: KCAPS1.2, KESC1.2, KLCTRL1.2, KLS1.2, KTAB1.2, U3.18 (PD0)
/COL1: KA1.2, KLMETA1.2, KONE1.2, KQ1.2, KZ1.2, U3.19 (PD1)
/COL2: KLALT1.2, KS1.2, KTWO1.2, KW1.2, KX1.2, U3.20 (PD2)
/COL3: KC1.2, KD1.2, KE1.2, KTHREE1.2, U3.21 (PD3)
/COL4: KF1.2, KFOUR1.2, KR1.2, KV1.2, U3.22 (PD5)
/COL5: KB1.2, KFIVE1.2, KG1.2, KSPACE1.2, KT1.2, U3.25 (PD4)
/COL6: KH1.2, KN1.2, KSIX1.2, KY1.2, U3.26 (PD6)
/COL7: KJ1.2, KM1.2, KSEVEN1.2, KU1.2, U3.27 (PD7)
/COL8: KCOMMA1.2, KEIGHT1.2, KI1.2, KK1.2, KRALT1.2, U3.28 (PB4)
/COL9: KL1.2, KNINE1.2, KO1.2, KPERIOD1.2, KRMETA1.2, U3.29 (PB5)
/COL10: KFSLASH1.2, KP1.2, KRCTRL1.2, KSC1.2, KZERO1.2, U3.30 (PB6)
/COL11: KAP1.2, KDASH1.2, KFN1.2, KLB1.2, KRS1.2, U3.31 (PC6)
/COL12: KEQUALS1.2, KRB1.2, KRETURN1.2, U3.32 (PC7)
/COL13: KBSLASH1.2, KBSPACE1.2, U3.33 (PE2)
/ROW0: KBSPACE1.1, KDASH1.1, KEIGHT1.1, KEQUALS1.1, KESC1.1, KFIVE1.1, KFOUR1.1, KNINE1.1, KONE1.1, KSEVEN1.1, KSIX1.1, KTHREE1.1, KTWO1.1, KZERO1.1, U3.12 (PB7)
/ROW1: KBSLASH1.1, KE1.1, KI1.1, KLB1.1, KO1.1, KP1.1, KQ1.1, KR1.1, KRB1.1, KT1.1, KTAB1.1, KU1.1, KW1.1, KY1.1, U2.1 (MISO), U3.11 (PB3(MISO))
/ROW2: KA1.1, KAP1.1, KCAPS1.1, KD1.1, KF1.1, KG1.1, KH1.1, KJ1.1, KK1.1, KL1.1, KRETURN1.1, KS1.1, KSC1.1, U2.4 (MOSI), U3.10 (PB2(MOSI))
/ROW3: KB1.1, KC1.1, KCOMMA1.1, KFSLASH1.1, KLS1.1, KM1.1, KN1.1, KPERIOD1.1, KRS1.1, KV1.1, KX1.1, KZ1.1, U2.3 (SCK), U3.9 (PB1(SCL))
/ROW4: KFN1.1, KLALT1.1, KLCTRL1.1, KLMETA1.1, KRALT1.1, KRCTRL1.1, KRMETA1.1, KSPACE1.1, U3.8 (PB0(SS))
unnamed: C1.1, C2.1, C3.1, U1.A1/B12 (GND), U1.B1/A12 (GND), U2.6 (GND), U3.5 (UGnd), U3.15 (GND), U3.23 (GND), U3.35 (GND), U3.43 (GND), U3.45 (GND), Y1.2, Y1.4
unnamed: C1.2, U3.6 (UCap)
unnamed: C2.2, U3.17 (XTAL1), Y1.1
unnamed: C3.2, U3.16 (XTAL2), Y1.3
unnamed: R1.1, U3.4 (D+)
unnamed: R1.2, U1.A6 (DP), U1.B6 (DP)
unnamed: R2.1, U3.3 (D-)
unnamed: R2.2, U1.A7 (DN), U1.B7 (DN)
unnamed: U1.A4/B9 (VBUS), U1.B4/A9 (VBUS), U2.2 (Vcc), U3.2 (UVcc), U3.7 (VBus), U3.14 (Vcc), U3.24 (AVcc), U3.34 (Vcc), U3.42 (AREF), U3.44 (AVcc)
unnamed: U2.5 (RST), U3.13 (~RESET)
